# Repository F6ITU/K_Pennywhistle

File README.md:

# K\_Pennywhistle

**A 20W HF amplifier by KE9H**

Pennywhistle is a linear amplifier based on a pair of Mitsubishi FET (RD16HHF1 or RD15HVF1) that was originally (17 years ago) used to boost the output power of the very first SDRs using the Hermes board.

Marketed as a kit by the TAPR, this amplifier—which is very easy to build—has long been out of production.

In the meantime, numerous variations have emerged, notably the famous G6ALU, which was used in Picastar transceivers.

This same amplifier is also integrated into the filter board of the Anan 100 series and serves as  driver for the RD100HHF1 output stage.

Why build such a clone in 2026 ?

* Because this design is proven and has been built in the thousands
* To complete the collection of OpenHPSDR board clones already available on this GitHub repository
* Because it can deliver either 4 to 7 W with RD06HVF1 transistors or 15 to 20 W in its original version—power levels perfectly suited for driving a higher-power amplifier (Munin 1 to 4 series, Munin 100, Munin 400...)
* Because it can easily complement a "barefoot" SDR outputting 0.5 to 1 W
* And because it is also compatible with the Ajax pre-driver module

It should be added that, technically speaking, it would be preferable to build a push-pull circuit using LDMOS transistors, such as the AFT05MS003... but the void left by the closure of NXP’s production facilities for high-frequency transistors and the resulting component shortage mean that a return —even a temporary one— to older technologies is far from unreasonable.

Finally, this amplifier is probably one of the simplest circuits available, allowing beginners to tackle building a linear amplifier without spending a fortune.

This project is licensed under the TAPR Open Hardware License and is the result of the work of Graham Haddock KE9H

It's design has been made using Kicad 10 opensource EDA.

Ibom can be downloaded from https://github.com/F6ITU/K\_Pennywhistle/blob/main/bom/ibom.html

All building and tuning instructions could be found in the original Pennywhistle documentation (https://github.com/TAPR/OpenHPSDR-SVN/blob/master/PennyWhistle/Documentation/PennyWhistle%20Manual%20V1.2.pdf)

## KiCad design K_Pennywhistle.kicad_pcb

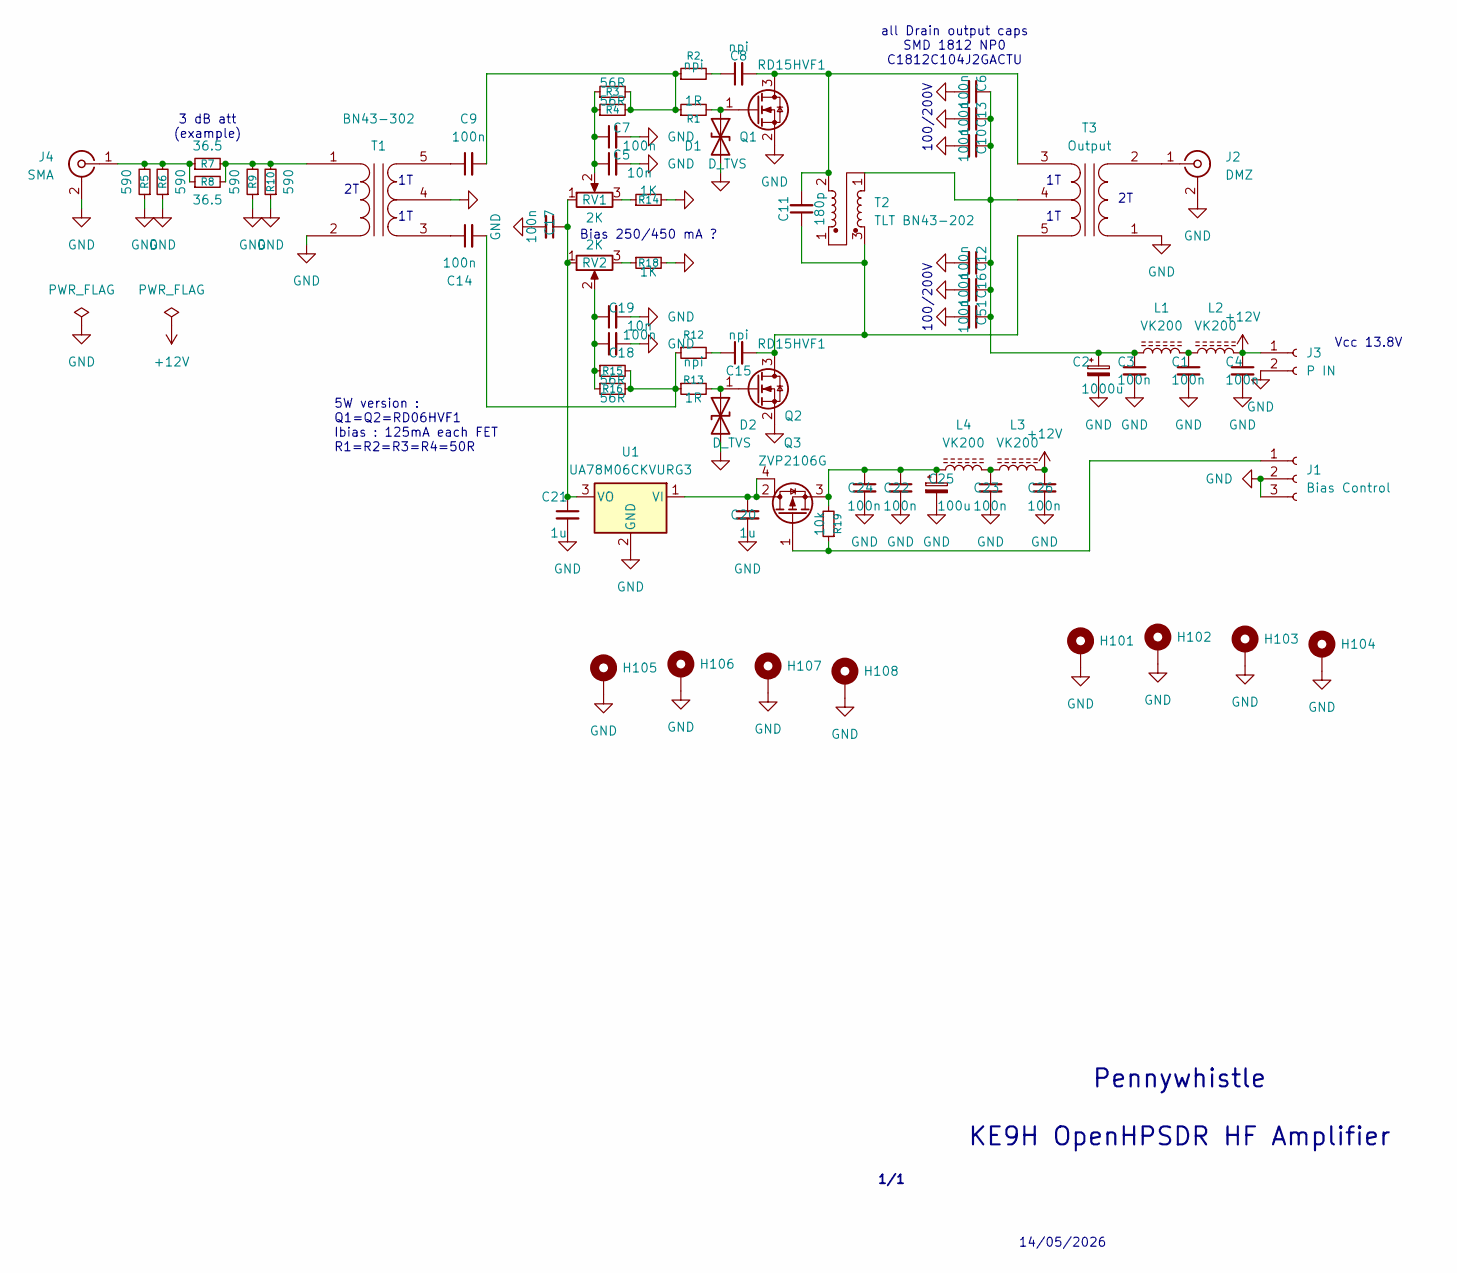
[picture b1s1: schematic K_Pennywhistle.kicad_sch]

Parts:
C1, C3, C4, C6, C7, C9, C10, C12, C13, C14, C16, C17, C18, C22, C23, C24, C26, C51: 100n; C_1206_3216Metric_Pad1.33x1.80mm_HandSolder
C2: 1000u; CP_Radial_D12.5mm_P7.50mm
C5, C19: 10n; C_0805_2012Metric_Pad1.18x1.45mm_HandSolder
C8, C15: npi; C_0805_2012Metric_Pad1.18x1.45mm_HandSolder
C11: 180p; C_1206_3216Metric_Pad1.33x1.80mm_HandSolder
C20, C21: 1u; C_0805_2012Metric_Pad1.18x1.45mm_HandSolder
C25: 100u; CP_Radial_D10.0mm_P5.00mm
D1, D2: D_TVS; D_0805_2012Metric
H101, H102, H103, H104: MountingHole_Pad; MountingHole_3.2mm_M3_Pad_Via
H105, H106, H107, H108: MountingHole_Pad; MountingHole_3.2mm_M3_ISO14580_Pad_TopBottom
J1: Bias Control; Molex_KK-254_AE-6410-03A_1x03_P2.54mm_Vertical
J2: DMZ; SMA_PINS
J3: P IN; AMASS_XT30U-F_1x02_P5.0mm_Vertical
J4: SMA; SMA_PINS
L1, L2, L3, L4: VK200; L_Axial_L12.8mm_D5.8mm_P5.08mm_Vertical_Fastron_HBCC
Q1, Q2: RD15HVF1; TO-220-3_Horizontal_TabDown
Q3: ZVP2106G; SOT-223-3_TabPin2
R1, R13: 1R; R_0805_2012Metric_Pad1.20x1.40mm_HandSolder
R2, R12: npi; R_0805_2012Metric_Pad1.20x1.40mm_HandSolder
R3, R4, R15, R16: 56R; R_0805_2012Metric_Pad1.20x1.40mm_HandSolder
R5, R6, R9, R10: 590; R_1812_4532Metric_Pad1.30x3.40mm_HandSolder
R7, R8: 36.5; R_1812_4532Metric_Pad1.30x3.40mm_HandSolder
R14, R18: 1K; R_0805_2012Metric_Pad1.20x1.40mm_HandSolder
R19: 10k; R_0805_2012Metric_Pad1.20x1.40mm_HandSolder
RV1, RV2: 2K; Potentiometer_Bourns_3266W_Vertical
T1: BN43-302; BN-61-202
T2: TLT BN43-202; BN-61-202
T3: Output; BN-61-202
U1: UA78M06CKVURG3; TO-252-3_TabPin2

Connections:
+12V: C4.1, C26.1, J3.1, L2.2, L3.2
GND: C1.2, C2.2, C3.2, C4.2, C5.2, C6.2, C7.2, C10.2, C12.2, C13.2, C16.2, C17.2, C18.2, C19.2, C20.2, C21.2, C22.2, C23.2, C24.2, C25.2, C26.2, C51.2, D1.2 (A2), D2.2 (A2), H101.1 (1_1), H102.1 (1_1), H103.1 (1_1), H104.1 (1_1), H105.1 (1_1), H106.1 (1_1), H107.1 (1_1), H108.1 (1_1), J1.2, J1.3, J2.2 (Ext), J3.2, J4.2 (Ext), Q1.2 (S), Q2.2 (S), R5.1, R6.1, R9.1, R10.1, R14.2, R18.2, T1.2 (AB), T1.4 (SC), T3.1 (AA), U1.2 (GND)
unnamed: C1.1, L1.2, L2.1
unnamed: C5.1, C7.1, R3.1, R4.1, RV1.2
unnamed: C8.1, R2.2
unnamed: C9.2, R1.1, R2.1, R3.2, R4.2
unnamed: C14.2, R12.1, R13.1, R15.2, R16.2
unnamed: C15.1, R12.2
unnamed: C18.1, C19.1, R15.1, R16.1, RV2.2
unnamed: C23.1, L3.1, L4.2
unnamed: D1.1 (A1), Q1.1 (G), R1.2
unnamed: D2.1 (A1), Q2.1 (G), R13.2
unnamed: J1.1, Q3.1 (G), R19.1
unnamed: J2.1 (In), T3.2 (AB)
unnamed: J4.1 (In), R5.2, R6.2, R7.1, R8.1
unnamed: C8.2, C11.2, Q1.3 (D), T2.2, T3.3 (SA)
unnamed: C11.1, C15.2, Q2.3 (D), T2.3, T3.5 (SB)
unnamed: C22.1, C24.1, C25.1, L4.1, Q3.3 (S), R19.2
unnamed: R14.1, RV1.3
unnamed: R18.1, RV2.3
unnamed: R7.2, R8.2, R9.2, R10.2, T1.1 (AA)
unnamed: C14.1, T1.3 (SA)
unnamed: C9.1, T1.5 (SB)
unnamed: C2.1, C3.1, C6.1, C10.1, C12.1, C13.1, C16.1, C51.1, L1.1, T2.1, T3.4 (SC)
unnamed: C20.1, Q3.2 (D), Q3.4 (D), U1.1 (VI)
unnamed: C17.1, C21.1, RV1.1, RV2.1, U1.3 (VO)

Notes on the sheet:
14/05/2026
Pennywhistle KE9H OpenHPSDR HF Amplifier
5W version : Q1=Q2=RD06HVF1 Ibias : 125mA each FET R1=R2=R3=R4=50R
100/200V
Vcc 13.8V
3 dB att (example)
Bias 250/450 mA ?
1/1
all Drain output caps SMD 1812 NP0 C1812C104J2GACTU

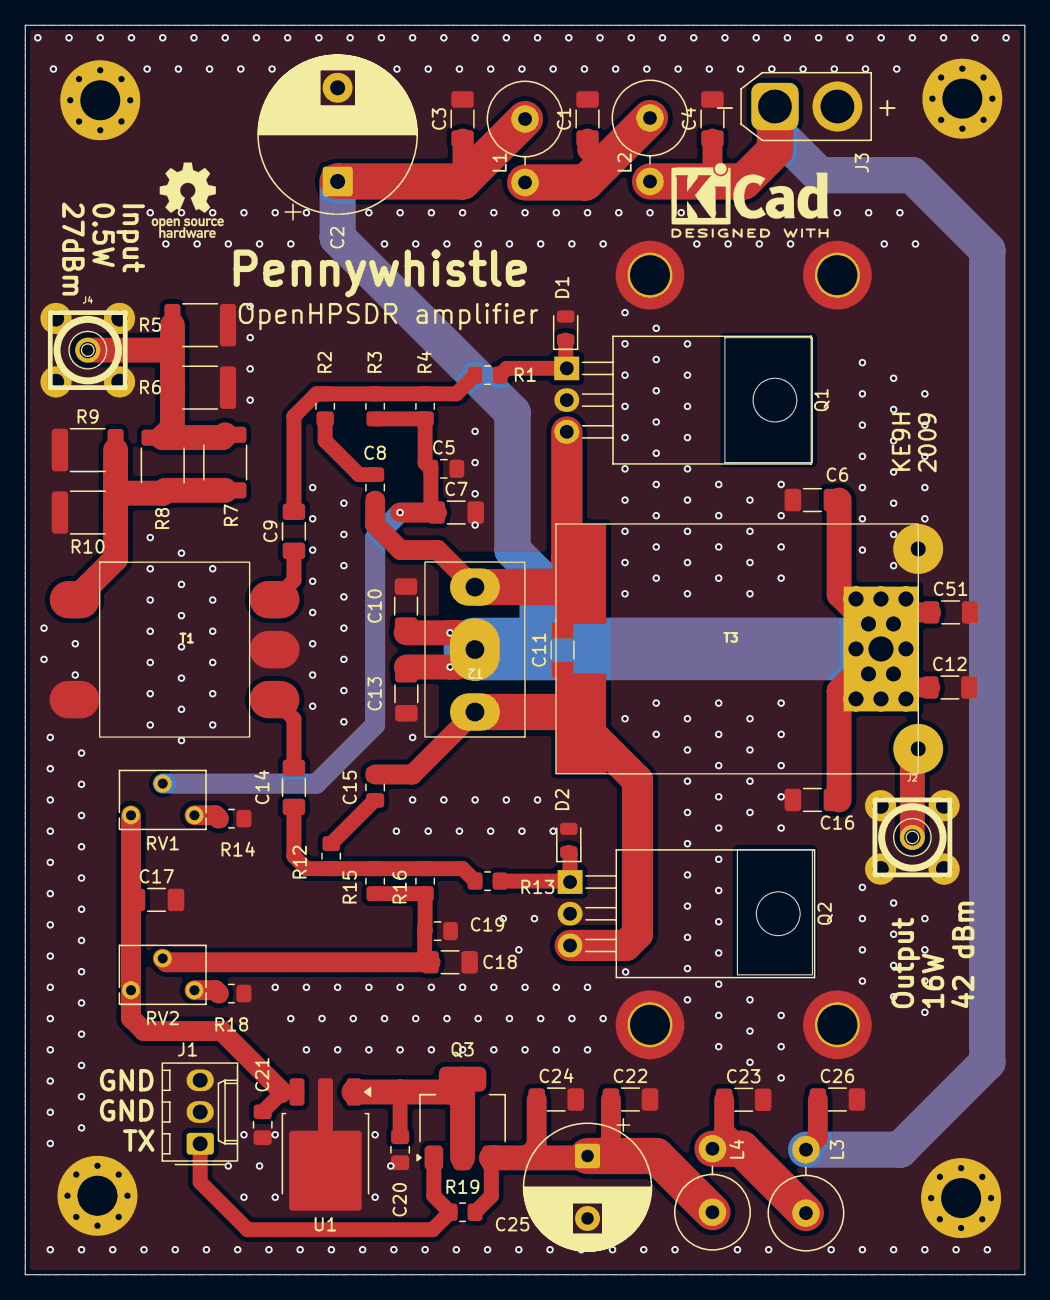
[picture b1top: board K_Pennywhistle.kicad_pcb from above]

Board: 2 copper layers, 80.0 x 100.0 mm, 71 parts (0 on the bottom side), 26 nets.

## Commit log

2026-05-12 initial release, no iBom, no routing yet
2026-05-12 first routed draft, fix some errors
2026-05-13 near RTM, iBom and 3D image added
2026-05-13 RTM (at last!)
2026-05-13 new Readme and image
2026-05-13 new README, iBom and Picture
2026-05-14 release, new Gerber, minor mods
2026-05-14 minor mods, new Gerber & iBom, schematic pdf,RTM
